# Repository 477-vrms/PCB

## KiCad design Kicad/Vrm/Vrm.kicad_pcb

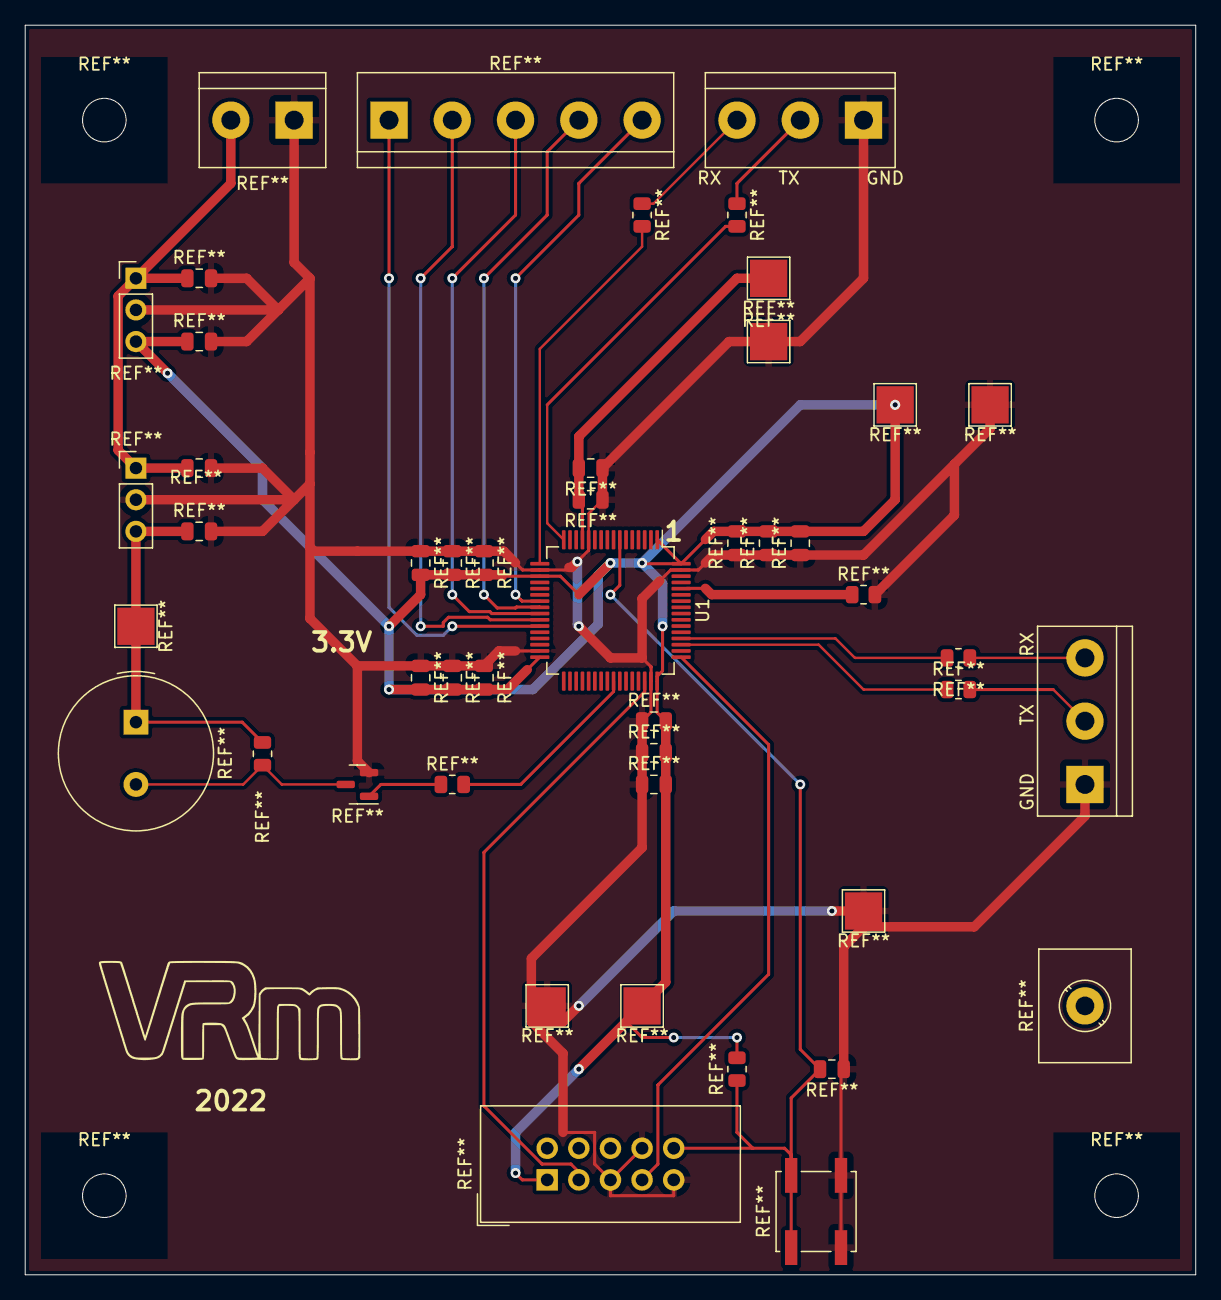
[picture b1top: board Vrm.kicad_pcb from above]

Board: 2 copper layers, 94.0 x 100.3 mm, 4 parts (0 on the bottom side), 2 nets.

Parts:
2022: LOGO; VRm_logo
   RX      TX       GND: PI UART; TerminalBlock_bornier-3_P5.08mm
GND     TX     RX: Servo UART; TerminalBlock_bornier-3_P5.08mm
U1: STM32F091RCTx; LQFP-64_10x10mm_P0.5mm

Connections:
GND: RX TX GND.1, GND TX RX.1, U1.12 (VSSA), U1.18 (VSS), U1.31 (VSS), U1.47 (VSS), U1.63 (VSS)
VDD: U1.1 (VBAT), U1.19 (VDD), U1.32 (VDD), U1.48 (VDDIO2), U1.64 (VDD)

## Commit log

2022-02-16 Updated Schematic
2022-02-23 Making Joe's PCB updates
2022-02-23 Added minor changes from manlab
2022-02-23 Power/GND beef up
2022-02-23 Pushed in decoupling caps
2022-02-25 Final Schematic
2022-02-25 Added UART resistors, new buzzer, UART breakout, and ground plane
2022-02-25 Added backups
2022-02-25 Added PUPD resistors, ground plane
2022-02-27 Update schematic
2022-02-28 real changes
2022-03-01 Added power modules to PCB
2022-03-02 Added VDD connections
2022-03-03 Added pads
2022-03-10 Last minute fixes from manlab
2022-03-11 Added Gerber file and logo
